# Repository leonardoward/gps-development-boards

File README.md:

# GPS Development Board - ANTENOVA M20050-1 and ATGM332D-5N31 #

A KiCad breakout board for evaluating two GPS modules side by side &mdash; the
[ANTENOVA M20050-1](https://www.digikey.com/en/products/detail/antenova/M20050-1/7931495)
and the
[ATGM332D-5N31](https://lcsc.com/product-detail/Satellite-Positioning-Modules_ZHONGKEWEI-ATGM332D-5N31_C128659.html)
&mdash; plus two footprints for 20&nbsp;mm coin&#8209;cell holders to keep the module's
backup RAM / almanac powered for a warm start.

## Context

This is one of the breakout boards made for the
**[EJA "Intelligent Popup Buoy"](https://hackaday.io/project/173457-2021-hdp-dream-team-eja)**
project (2021 Hackaday Dream Team). Each candidate part for the
[EJA&nbsp;M](https://github.com/leonardoward/eja-m-pcb-design) board was first tried on a
small dedicated PCB. Both GPS modules speak plain **NMEA over UART** and are wired to
identical header pinouts here, so the same ESP32 firmware runs against either one.
The **ATGM332D-5N31** was the module chosen for EJA&nbsp;M.

## Table of Contents

1. [Schematic](#schematic)
2. [Bill of Materials](#bill-of-materials)
3. [3D Model](#3d-model)
4. [Firmware and Testing](#firmware-and-testing)
5. [Repository Layout](#repository-layout)

## Schematic ##

### ANTENOVA M20050-1 ###

### ATGM332D-5N31 ###

Each module has a decoupling capacitor, a U.FL connector for an external active
antenna, a coin&#8209;cell backup input, and UART / I2C / `IND` (fix indicator) broken
out to headers.

### Additional Coin Battery Holders ###

Two 20&nbsp;mm coin&#8209;cell holder footprints (a
[Linx BAT-HLD-001](https://www.digikey.com/en/products/detail/linx-technologies-inc/BAT-HLD-001-THM/3044009)
retainer and a
[Keystone 1066](https://www.digikey.com/en/products/detail/keystone-electronics/1066/303562)
open holder) so the mechanically better one can be picked for the buoy.

## Bill of Materials ##

| Reference | Quantity |
| ------------- | ------------- |
| [10 µF ±10% 6.3V Ceramic Capacitor X5R 0805 (2012 Metric)](https://www.digikey.com/en/products/detail/samsung-electro-mechanics/CL21A106KQCLNNC/3888062)  | 4 |
| [Red 630nm LED Indication - Discrete 1.9V 0805 (2012 Metric)](https://www.digikey.com/en/products/detail/w%C3%BCrth-elektronik/150080SS75000/4489921)  | 1 |
| [U.FL (UMCC) Connector Receptacle, Male Pin 50Ohm Surface Mount Solder](https://www.digikey.com/en/products/detail/hirose-electric-co-ltd/U-FL-R-SMT-1-10/2391570) | 2 |
| [Battery Retainer Coin, 20.0mm 1 Cell PC Pin](https://www.digikey.com/en/products/detail/linx-technologies-inc/BAT-HLD-001-THM/3044009) | 1 |
| [Battery Holder (Open) Coin, 20.0mm 1 Cell PC Pin](https://www.digikey.com/en/products/detail/keystone-electronics/1066/303562) | 1 |
| [Unshielded Multilayer Inductor 100mOhm Max 0805 (2012 Metric)](https://www.digikey.com/en/products/detail/abracon-llc/AIMC-0805-1N8S-T/2662915) | 1 |
| [1K ±1% 0.125W, 1/8W Chip Resistor 0805 (2012 Metric)](https://www.digikey.com/en/products/detail/panasonic-electronic-components/ERJ-6ENF1001V/111281) | 2 |
| [220 Ohms ±5% 0.125W, 1/8W Chip Resistor 0805 (2012 Metric)](https://www.digikey.com/en/products/detail/yageo/RC0805JR-07220RL/728283) | 1 |
| [0 Ohms Jumper 0.125W, 1/8W Chip Resistor 0805 (2012 Metric)](https://www.digikey.com/en/products/detail/yageo/RC0805JR-070RL/728216) | 1 |
| [ATGM332D-5N31 GNSS GPS+BDS Satellite Positioning Module](https://lcsc.com/product-detail/Satellite-Positioning-Modules_ZHONGKEWEI-ATGM332D-5N31_C128659.html) | 1 |
| [Antenova M20050-1 RF Receiver GPS 1.575GHz -165dBm](https://www.digikey.com/en/products/detail/antenova/M20050-1/7931495) | 1 |
| [Conn Header 40POS 2.54](https://www.digikey.com/en/products/detail/3m/2340-6111TG/1237275) | 1 |

A machine-readable BOM is in `gps-testing-board/gps-testing-board.csv`.

## 3D Model ##

## Firmware and Testing ##

`Firmware/` has an Arduino sketch for each module (`esp32_atgm332d/` and
`esp32_antenova_m20050/`). Both are the same code with a different banner; only one
module is exercised at a time.

* The ESP32's `Serial2` runs at **9600 baud** on **GPIO16 (RX) / GPIO17 (TX)**, wired
  to the module's UART header.
* The [`FuGPS`](https://github.com/fu-hsi/FuGPS) library parses the NMEA stream. The
  sketch asks the module for `RMC + GGA` sentences
  (`FUGPS_PMTK_API_SET_NMEA_OUTPUT_RMCGGA`).
* When a fix is available it prints fix quality, satellite count, HDOP, altitude and a
  ready&#8209;to&#8209;click `google.com/maps` link with the current latitude / longitude;
  if the module goes quiet for ~10&nbsp;s it prints a "not responding" warning.

Wire the module header to the ESP32 (`VIN`&rarr;`3V3`, `GND`&rarr;`GND`,
`TX`&rarr;`GPIO16`, `RX`&rarr;`GPIO17`), fit an active antenna on the U.FL connector,
open the matching sketch in the Arduino IDE (ESP32 board support + the `FuGPS` library
installed) and watch the serial monitor at 115200 baud. A first fix outdoors takes a
few minutes cold, seconds warm with the backup cell fitted.

## Repository Layout

```
README.md
LICENSE                              Apache 2.0
Schematic v1.0.pdf                   exported schematic
Images/                              schematics, 3D renders, board photos
Firmware/
  esp32_atgm332d/                    Arduino sketch, ATGM332D-5N31
  esp32_antenova_m20050/             Arduino sketch, ANTENOVA M20050-1
gps-testing-board/                   KiCad project
  gps-testing-board.pro/.sch/.kicad_pcb
  gps-testing-board.csv              BOM
  Symbols/ Footprints/ 3D/           project-local libraries
  Gerber/                            fabrication output
  Exports/                           STEP model
```

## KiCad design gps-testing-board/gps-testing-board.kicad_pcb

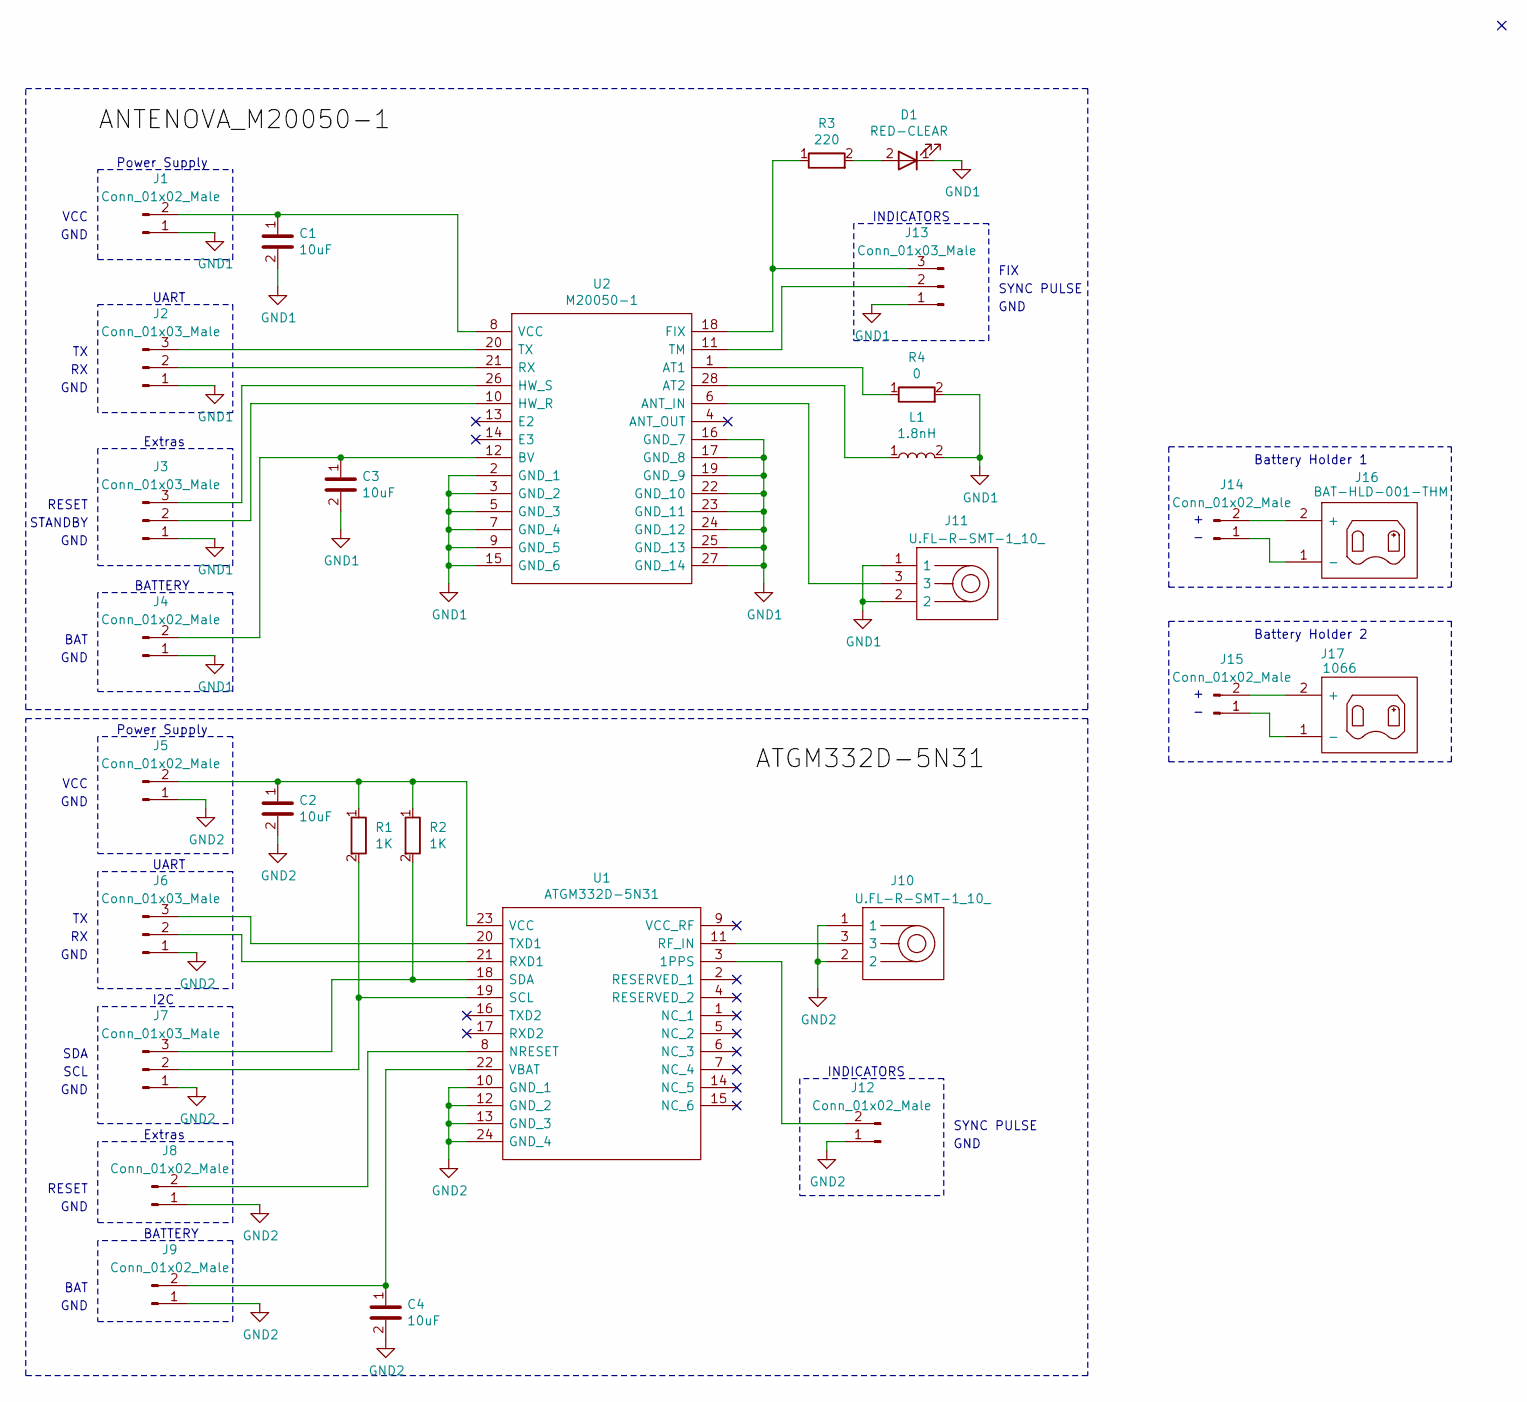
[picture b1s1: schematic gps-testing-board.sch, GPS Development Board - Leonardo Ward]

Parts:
C1, C2, C3, C4: 10uF; C_0805_2012Metric; Manufacturer Part Number CL21A106KQCLNNC
D1: RED-CLEAR; LED_0805_2012Metric; Manufacturer Part Number 150080SS75000
J1, J4, J5, J8, J9, J12, J14, J15: Conn_01x02_Male; PinSocket_1x02_P2.54mm_Vertical
J2, J3, J6, J7, J13: Conn_01x03_Male; PinSocket_1x03_P2.54mm_Vertical
J10, J11: U.FL-R-SMT-1_10_; Manufacturer_Part_Number U.FL-R-SMT-1(10); Mouser Part Number 798-U.FL-R-SMT-110
J16: BAT-HLD-001-THM; BATHLD001THM; Manufacturer_Part_Number BAT-HLD-001-THM
J17: 1066; BAT-1066; Manufacturer_Part_Number 1066
L1: 1.8nH; L_0805_2012Metric; Manufacturer Part Number AIMC-0805-1N8S-T
R1, R2: 1K; R_0805_2012Metric; Manufacturer Part Number ERJ-6ENF1001V
R3: 220; R_0805_2012Metric; Manufacturer Part Number RC0805JR-07220RL
R4: 0; R_0805_2012Metric; Manufacturer Part Number RC0805JR-070RL
U1: ATGM332D-5N31; ATGM332D5N31; Manufacturer_Part_Number ATGM332D-5N31; LCSC C128659
U2: M20050-1; M200501; Manufacturer_Part_Number M20050-1

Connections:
GND1: C1.2, C3.2, D1.1 (K), J1.1, J2.1, J3.1, J4.1, J11.1, J11.2, J13.1, L1.2, R4.2, U2.2 (GND_1), U2.3 (GND_2), U2.5 (GND_3), U2.7 (GND_4), U2.9 (GND_5), U2.15 (GND_6), U2.16 (GND_7), U2.17 (GND_8), U2.19 (GND_9), U2.22 (GND_10), U2.23 (GND_11), U2.24 (GND_12), U2.25 (GND_13), U2.27 (GND_14)
GND2: C2.2, C4.2, J5.1, J6.1, J7.1, J8.1, J9.1, J10.1, J10.2, J12.1, U1.10 (GND_1), U1.12 (GND_2), U1.13 (GND_3), U1.24 (GND_4)
unnamed: C1.1, J1.2, U2.8 (VCC)
unnamed: C2.1, J5.2, R1.1, R2.1, U1.23 (VCC)
unnamed: C3.1, J4.2, U2.12 (BV)
unnamed: C4.1, J9.2, U1.22 (VBAT)
unnamed: D1.2 (A), R3.2
unnamed: J2.2, U2.21 (RX)
unnamed: J2.3, U2.20 (TX)
unnamed: J3.2, U2.10 (HW_R)
unnamed: J3.3, U2.26 (HW_S)
unnamed: J6.2, U1.21 (RXD1)
unnamed: J6.3, U1.20 (TXD1)
unnamed: J7.2, R1.2, U1.19 (SCL)
unnamed: J7.3, R2.2, U1.18 (SDA)
unnamed: J8.2, U1.8 (NRESET)
unnamed: J10.3, U1.11 (RF_IN)
unnamed: J11.3, U2.6 (ANT_IN)
unnamed: J12.2, U1.3 (1PPS)
unnamed: J13.2, U2.11 (TM)
unnamed: J13.3, R3.1, U2.18 (FIX)
unnamed: J14.1, J16.1 (-)
unnamed: J14.2, J16.2 (+)
unnamed: J15.1, J17.1 (-)
unnamed: J15.2, J17.2 (+)
unnamed: L1.1, U2.28 (AT2)
unnamed: R4.1, U2.1 (AT1)

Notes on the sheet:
VCC
GND
UART
Power Supply
Extras
RESET
STANDBY
BATTERY
BAT
INDICATORS
FIX
SYNC PULSE
SDA
SCL
I2C
Battery Holder 1
Battery Holder 2

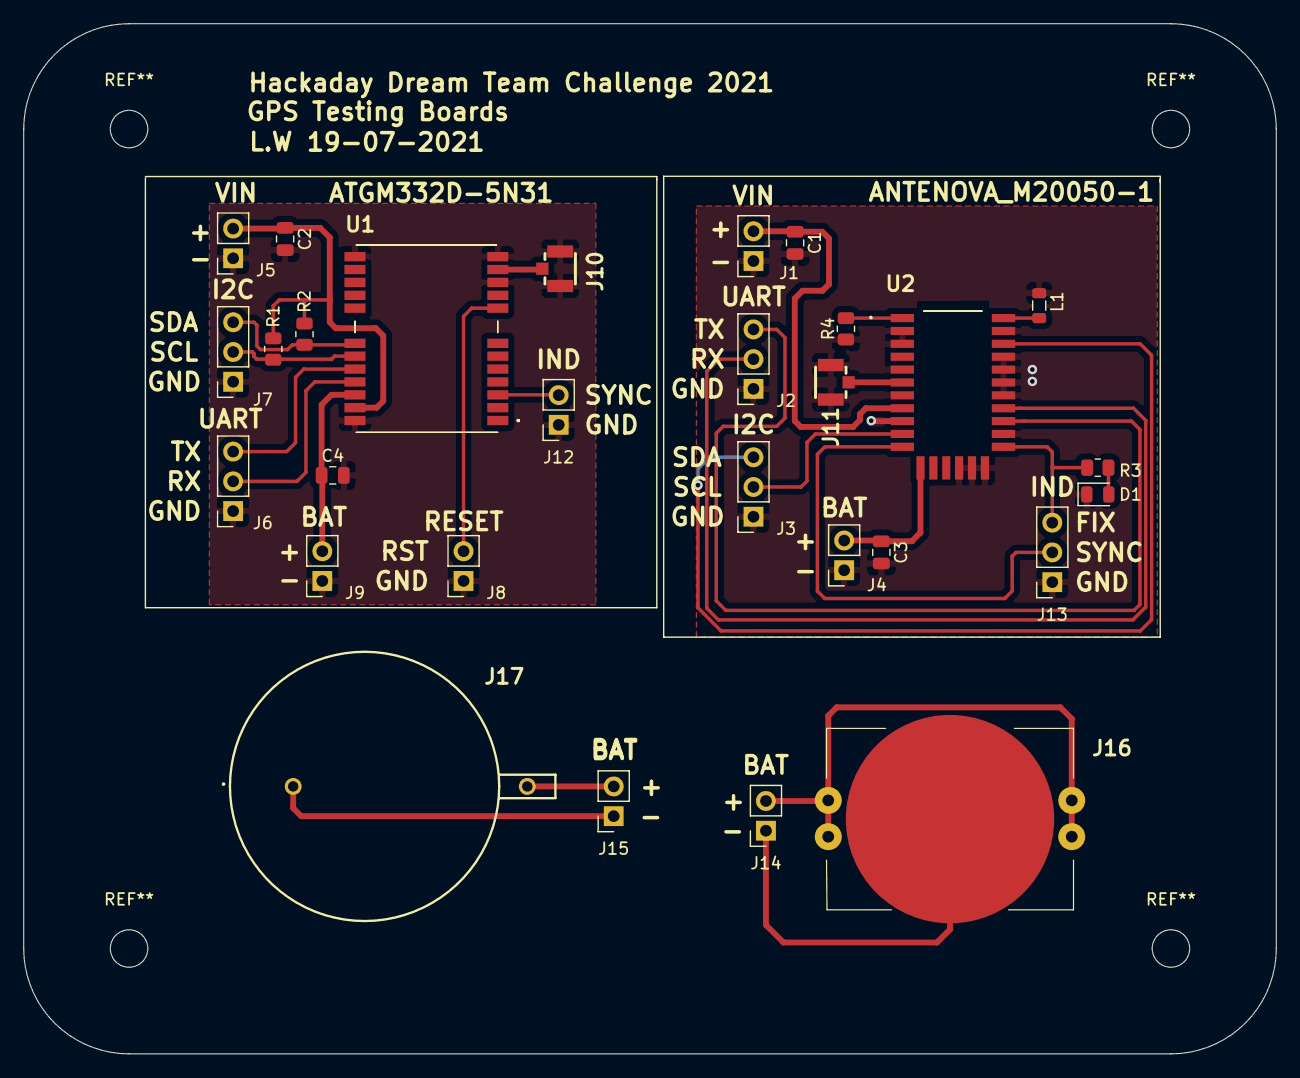
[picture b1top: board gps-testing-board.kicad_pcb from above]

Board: 2 copper layers, 107.0 x 88.0 mm, 29 parts (0 on the bottom side), 27 nets.

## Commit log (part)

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2021-07-15 Added schematic for Antenova M20050-1
2021-07-19 Added PCB and battery holders
2021-07-19 Added 3D models
2021-07-20 Added IDFv3 and Gerber
2021-08-06 Added Bill of Materials and images to README
2021-08-19 Added firmware
2021-11-05 Added image of the PCB
